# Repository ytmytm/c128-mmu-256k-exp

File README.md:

# C128 256K RAM expansion MMU daughterboard

This work is based on a project developed by Marko Mäkelä and Pekka Pessi that described expanding Commodore 128 memory to 256 or 512/1024 kilobytes of RAM.

Two KiCad projects capture schematic and PCB for 256KB expansion only.

This is a daughterboard meant to be plugged into U7 socket to raise the original MOS 8722 MMU chip and add a second one to generate `/CAS` signals for RAM banks 2 and 3. The challenge was to make it narrow enough to fit into C128DCR - there is not much space near MMU socket between power connector, power supply and SID.

For the full description of the project please read the [original documentation on zimmers.net](http://www.zimmers.net/anonftp/pub/cbm/documents/projects/memory/c128/1028/index.html).

Be warned that PS/HTML/PDF versions contain a small error (read below).

## Background

I have built this expansion by following the [TXT document](http://www.zimmers.net/anonftp/pub/cbm/documents/projects/memory/c128/1028/1028.txt) in late March 1999 and it has served me ever since.

There is not much software that uses RAM banks 2 and 3 but [I wrote some software on my own for GEOS](https://github.com/ytmytm/c64-geos-ramdrives). This kind of expansion is also emulated by VICE.

Now, over 20 years later I'm not happy with the soldering job I did in my late teens. Connections became brittle and the whole mess of wires from this and other mods makes it very difficult to repair in case something goes wrong.

These days it's so easy and cheap to order professionally manufactured PCBs that I decided to revisit the project.

## TTL project

[c128-mmu-exp-ttl](c128-mmu-exp-ttl/) folder contains KiCad 6.0 project that captures the design from the original description. With all chips moved to a daughterboard simplifications could be made and the only additional signals from the mainboard are:

- `/RAMCAS0` and `/RAMCAS1` (input from pins of U9)
- `/RAMCAS0` and `/RAMCAS1` (output to old RAM, U9 board)
- `/RAMCAS2` and `/RAMCAS3` (output to new RAM)

The original document calls for desoldering U9 and soldering some wires to the board and raised legs. However it's much more convenient to raise one leg of R29 and R30 and tie there. In case you really want to go with connecting to U9 please keep in mind that the same signals are connected to different pins on C128(D) and C128DCR.

### Design correction

I remembered that I had stumbled on a mistake in the original documentation, I just didn't leave for myself enough information what it was. This is why I started with TTL version to duplicate exactly the reference design and understand how it works.

The problem is with IC7 (74LS02) connection to IC8 (4066). IC8 (4066) pins 6 (E3) and 12 (E4) were swapped on the original schematic and in the description. 
Fortunately the authors described not only the circuit but also the theory of operation.
To make it work as described in section 3.1.1:

> pass D7 into D6 of new MMU, except for $D505 (then pass D6 as D6)

IC8 pin 6 has to be connected to IC7 pin 3 (NAND output) and IC8 pin 12 has to be connected to IC7 pins 1 and 2 (NAND input) and IC6 (74LS138) pin 10 (/O5).

Documentation in PS/PDF/HTML format has this problem. TXT version has correct ASCII drawing of the schematic, but the same mistake in description.

[Corrected schematic is here](c128-mmu-exp-ttl/plots/c128-mmu-exp.pdf). This PCB design was not tested - I never meant to build it.
There is no way to make it fit into C128DCR and keep dimensions within cheap 10x10cm board size.

## GAL project

[c128-mmu-exp-gal](c128-mmu-exp-gal/) folder contains KiCad 6.0 project for a MMU daughterboard with all the glue logic moved to a GAL22V10.

[c128-mmu-exp-gal/plots](c128-mmu-exp-gal/plots) folder contains Gerber files for manufacturing and [schematic](c128-mmu-exp-gal/plots/c128-mmu-exp.pdf).

[gal-jed](gal-jed) folder contains GAL logic prepared in WinCUPL

- JED file to be flashed into GAL
- PLD, DOC files with logic equations
- SI file with simulation cases for complete testing

### Flashing GALs

Flash the [JED](gal-jed/C128_MMU256K.jed) file into a GAL22V10. These devices are themselves obsolete. Chips that I had from an unknown Chinese source were clearly refurbished. ATMEL markings started to rub off even without using alcohol.

I have used TL866 II Plus to flash them. Remember to turn off "Encrypt chip" and "Lock bit" options.

### PCBS

Make sure to solder round pin headers under 48-pin DIP sockets first.

### Installation in C128DCR

#### Step 1

First test can be done right away. Just plug in the daughterboard with MMU installed into U7 socket. GAL is not yet necessary. The computer should start normally. The new PCB fits nicely just between SID and the power socket. Check carefully if the daughterboard is plugged correctly with no shifted pins hanging outside the U7 socket.

#### Step 2

Now we need to tie into `/RAMCAS0` and `/RAMCAS1` signals that go out of U9. The easiest way to do it is to raise one leg of R29/R30 and connect one wire to each raised leg and another one to pad on the mainboard.

- `/RAMCAS` input - from U9 chip side goes to PCB J1: bank0 (related to R29) to round pad, bank1 (related to R30) to square pad
- `/RAMCAS` output - from U9 board side goes to PCB J2: bank0 (related to R29, U38 pin 16) to round pad, bank1 (related to R30, U39 pin 16) to square pad

You can see how yellow wires - connected to R29/R30 leg - go to J1 while red wires - connected to pads near the edge of the board - go to J2.

Another way to put it: J1 connects to U9 pins, J2 connects to RAM (U38-41) pin 16

At this stage, with both MMUs and GAL installed the computer should work normally. There should be one difference: machine monitor commands `M 24000 24080` or `M 34000 34080` should show randomly changing values from unconnected RAM banks 2 and 3 instead of mirroring data from banks 0 and 1.

#### Step 3

Finally signals from J3 should be connected to `/CAS` pins of new DRAM chips piggy-backed on existing U38-U41 chips. In my case, I already had another board with [SRAM replacement for C128DCR system RAM](https://oshwlab.com/mwitkowiak/sram-test_copy).

### Installation in C128D

I don't own a flat C128, nor a C128D with a case. All I have is a rescued C128D board, so I don't really know if a populated daughterboard will fit inside a case and under the keyboard.

The daughterboard doesn't reach capacitors in the back and just barely covers CIA in the front.

I'm using SRAM here as well - two [SaRuMan 128 modules](https://c-128.freeforums.net/thread/928/saruman-c128-static-replacement-board).
I decided to make things even easier for myself and removed R29/R30 completely.

Red wires are connected to U3 and go to J1 while blue wires are connected to RAM chips `/CAS` pins (15) and go to J2.

Green wires connect SRAM modules with J3.

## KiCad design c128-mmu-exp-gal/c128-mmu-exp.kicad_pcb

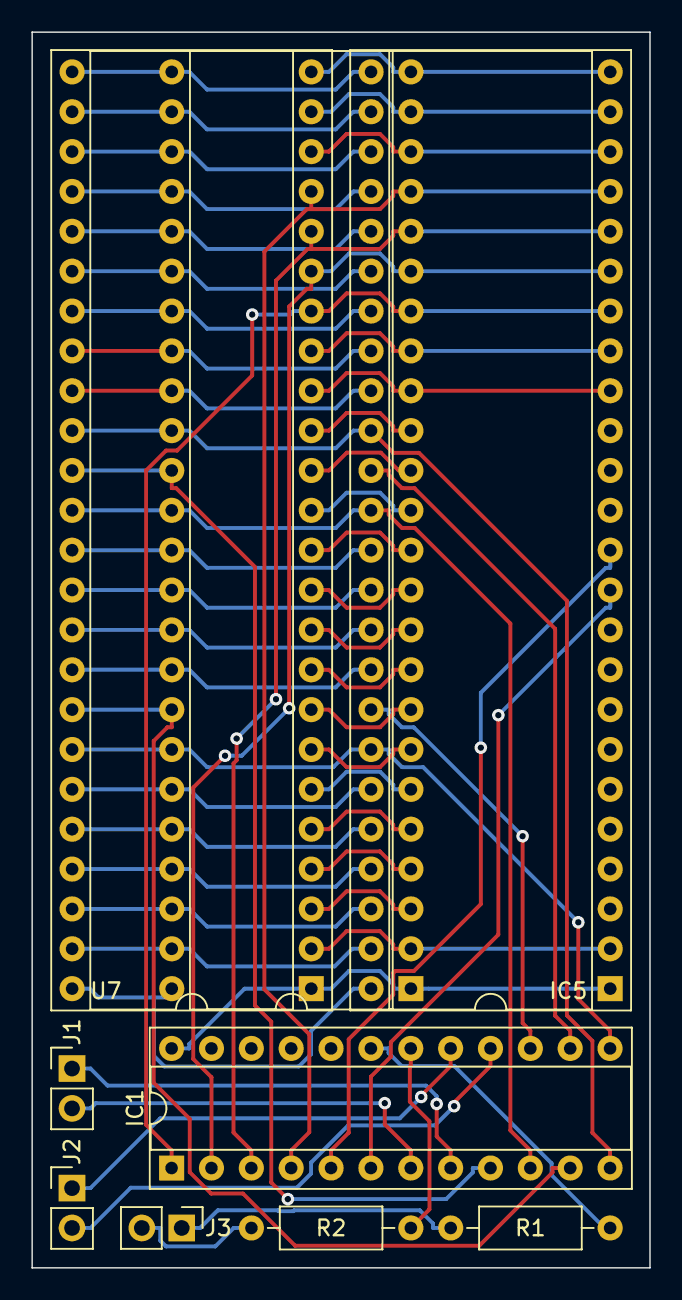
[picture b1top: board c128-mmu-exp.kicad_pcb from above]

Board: 2 copper layers, 39.4 x 78.7 mm, 9 parts (0 on the bottom side), 60 nets.

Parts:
IC1: GAL22V10; DIP-24_W7.62mm_Socket
IC5: NEW MMU; DIP-48_W15.24mm_Socket
J1: U9-CHIP; PinHeader_1x02_P2.54mm_Vertical
J2: U9-SOCKET; PinHeader_1x02_P2.54mm_Vertical
J3: TO NEW RAM CHIPS; PinHeader_1x02_P2.54mm_Vertical
R1, R2: 68; R_Axial_DIN0207_L6.3mm_D2.5mm_P10.16mm_Horizontal
U7: OLD MMU; DIP-48_W15.24mm_Socket
U7_SOCKET1: MMU SOCKET PINS; DIP-48_W15.24mm

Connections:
/40/~80: IC5.48 (40/~80), U7.48 (40/~80), U7_SOCKET1.48 (40/~80)
/A0: IC1.1 (I1), IC5.18 (A0), U7.18 (A0), U7_SOCKET1.18 (A0)
/A1: IC1.2 (I2), IC5.19 (A1), U7.19 (A1), U7_SOCKET1.19 (A1)
/A2: IC1.3 (I3), IC5.20 (A2), U7.20 (A2), U7_SOCKET1.20 (A2)
/A3: IC1.4 (I4), IC5.21 (A3), U7.21 (A3), U7_SOCKET1.21 (A3)
/A5/A4: IC5.22 (A5/A4), U7.22 (A5/A4), U7_SOCKET1.22 (A5/A4)
/A7/A6: IC5.23 (A7/A6), U7.23 (A7/A6), U7_SOCKET1.23 (A7/A6)
/A8: IC5.24 (A8), U7.24 (A8), U7_SOCKET1.24 (A8)
/A9: IC5.25 (A9), U7.25 (A9), U7_SOCKET1.25 (A9)
/A10: IC5.26 (A10), U7.26 (A10), U7_SOCKET1.26 (A10)
/A11: IC5.27 (A11), U7.27 (A11), U7_SOCKET1.27 (A11)
/A12: IC5.28 (A12), U7.28 (A12), U7_SOCKET1.28 (A12)
/A13: IC5.29 (A13), U7.29 (A13), U7_SOCKET1.29 (A13)
/A14: IC5.30 (A14), U7.30 (A14), U7_SOCKET1.30 (A14)
/A15: IC5.31 (A15), U7.31 (A15), U7_SOCKET1.31 (A15)
/AEC: IC5.16 (AEC), U7.16 (AEC), U7_SOCKET1.16 (AEC)
/D0: IC1.9 (I9), U7.35 (D0), U7_SOCKET1.35 (D0)
/D0_{IC5}: IC1.14 (I/O/Q14), IC5.35 (D0)
/D1: IC1.10 (I10), IC5.36 (D1), U7.36 (D1), U7_SOCKET1.36 (D1)
/D2: IC5.37 (D2), U7.37 (D2), U7_SOCKET1.37 (D2)
/D3: IC5.38 (D3), U7.38 (D3), U7_SOCKET1.38 (D3)
/D4: IC5.39 (D4), U7.39 (D4), U7_SOCKET1.39 (D4)
/D5: IC5.40 (D5), U7.40 (D5), U7_SOCKET1.40 (D5)
/D6: IC1.11 (I11), U7.41 (D6), U7_SOCKET1.41 (D6)
/D6_{IC5}: IC1.15 (I/O/Q15), IC5.41 (D6)
/D7: IC1.13 (I13), IC5.42 (D7), U7.42 (D7), U7_SOCKET1.42 (D7)
/MS0: U7.15 (MS0), U7_SOCKET1.15 (MS0)
/MS1: U7.14 (MS1), U7_SOCKET1.14 (MS1)
/MS2,~IOSEL: U7.13 (MS2,~{IOSEL), U7_SOCKET1.13 (MS2,~{IOSEL)
/MS3: IC5.47 (MS3), U7.47 (MS3), U7_SOCKET1.47 (MS3)
/MUX: IC5.17 (MUX), U7.17 (MUX), U7_SOCKET1.17 (MUX)
/PHI_{IN}: IC5.33 (PHI_{IN}), U7.33 (PHI_{IN}), U7_SOCKET1.33 (PHI_{IN})
/R/~W: IC5.32 (R/~W), U7.32 (R/~W), U7_SOCKET1.32 (R/~W)
/TA8: U7.10 (TA8), U7_SOCKET1.10 (TA8)
/TA9: U7.9 (TA9), U7_SOCKET1.9 (TA9)
/TA10: U7.8 (TA10), U7_SOCKET1.8 (TA10)
/TA11: U7.7 (TA11), U7_SOCKET1.7 (TA11)
/TA12: U7.6 (TA12), U7_SOCKET1.6 (TA12)
/TA13: U7.5 (TA13), U7_SOCKET1.5 (TA13)
/TA14: U7.4 (TA14), U7_SOCKET1.4 (TA14)
/TA15: U7.3 (TA15), U7_SOCKET1.3 (TA15)
/~CAS0_{NEW}: IC1.5 (I5), IC5.12 (~CAS0)
/~CAS0: U7.12 (~CAS0), U7_SOCKET1.12 (~CAS0)
/~CAS1_{NEW}: IC1.6 (I6), IC5.11 (~CAS1)
/~CAS1: U7.11 (~CAS1), U7_SOCKET1.11 (~CAS1)
/~EXROM: IC5.46 (~EXROM), U7.46 (~EXROM), U7_SOCKET1.46 (~EXROM)
/~FSDIR: IC5.44 (~FSDIR), U7.44 (~FSDIR), U7_SOCKET1.44 (~FSDIR)
/~GAME: IC5.45 (~GAME), U7.45 (~GAME), U7_SOCKET1.45 (~GAME)
/~RAMCAS0_{IN}: IC1.7 (I7), J1.2
/~RAMCAS0_{OUT}: IC1.16 (I/O/Q16), J2.2
/~RAMCAS1_{IN}: IC1.8 (I8), J1.1
/~RAMCAS1_{OUT}: IC1.17 (I/O/Q17), J2.1
/~RAMCAS2: J3.2, R2.2
/~RAMCAS3: J3.1, R1.2
/~RESET: IC5.2 (~RESET), U7.2 (~RESET), U7_SOCKET1.2 (~RESET)
/~Z80EN: IC5.43 (~Z80EN), U7.43 (~Z80EN), U7_SOCKET1.43 (~Z80EN)
GND: IC1.12 (GND), IC5.34 (VSS), U7.34 (VSS), U7_SOCKET1.34 (VSS)
unnamed: IC1.18 (I/O/Q18), R2.1
unnamed: IC1.19 (I/O/Q19), R1.1
VCC: IC1.24 (VCC), IC5.1 (VDD), U7.1 (VDD), U7_SOCKET1.1 (VDD)

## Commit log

2022-07-17 images
2022-07-18 edits
2022-10-02 Update README.md
    link to 256K SRAM in C128DCR project
